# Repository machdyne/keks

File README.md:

# Keks Game Console

Keks is a 32-bit FPGA-based video game console and computer designed as a fun educational platform for teaching and learning about computers, electronics, FPGAs and programming.

This repo contains schematics, PCB layouts, pinouts, firmware, gateware, documentation and a 3D printable case.

Find more information on the [Keks product page](https://machdyne.com/product/keks-game-console/).

## Blinky 

Building the blinky example requires [Yosys](https://github.com/YosysHQ/yosys), [nextpnr-ice40](https://github.com/YosysHQ/nextpnr) and [IceStorm](https://github.com/YosysHQ/icestorm).

Assuming they are installed, you can simply type `make` to build the gateware, which will be written to output/blinky.bin. You can then connect the USB-C port to your computer and use the latest version of [ldprog](https://github.com/machdyne/ldprog) to write the gateware to the device.

## Programming

The RP2040 firmware and FPGA SRAM can be programmed over the USB-C port.

Configure the FPGA SRAM:

```
$ ldprog -k -s blinky.bin
```

It should also be possible to transfer gateware and games to the MicroSD card over the USB-C port but this is not yet implemented.

## Games

* [pong](games/pong)

## Firmware

Keks ships with RP2040 [firmware](firmware) based on the [Müsli](https://github.com/machdyne/musli) firmware which allows it to communicate with [ldprog](https://github.com/machdyne/ldprog).

The firmware is responsible for initializing the system, [configuring and outputting the RP clock](https://www.raspberrypi.com/documentation/pico-sdk/hardware.html#hardware_clocks), configuring the FPGA and detecting USB HID events.

The RP clock (CLK\_RP) is 48MHz by default. Keks also has a 100 MHz oscillator on board (CLK\_100).

*The following description is still under development and may change.*

*If an inserted FAT-formatted MicroSD card contains a bitstream file in the root directory named GATEWARE.BIN it will be used to configure the FPGA after power-on.*

*The RP2040 firmware also acts as an SPI master and sends updates to the FPGA when the status of the gamepads/joysticks change.*

In addition to the 4 CSPI signals and CLK\_RP there are 6 other signals connected to both the RP2040 and the FPGA: RP\_TX, RP\_RX, and RP\_INT, CDONE, CRESET and BTN.

### Updating the Firmware

To build the latest firmware you will need to install the [Raspberry Pi Pico SDK](https://github.com/raspberrypi/pico-sdk).

Set the `PICO_SDK_PATH` environment variable to your SDK path.

```
$ git clone https://github.com/machdyne/keks
$ cd keks/firmware/keks
$ mkdir build
$ cd build
$ cmake ..
$ make
```

The firmware can then be updated by holding down the (small) BOOTSEL button, connecting the USB-C port to your computer, and then dragging and dropping a new UF2 file to the device filesystem.

## DDMI

See this [my_hdmi_device fork](https://github.com/machdyne/my_hdmi_device) for an example of outputting video on the DDMI port.

See this [SmolDVI fork](https://github.com/machdyne/SmolDVI) for another example of outputting video on the DDMI port.

## Pinouts

 * [DDMI](https://github.com/machdyne/ddmi)

## License

The contents of this repo are released under the [Lone Dynamics Open License](LICENSE.md) with the following exceptions:

- The KiCad design files contain parts of the [kicad-pmod](https://github.com/mithro/kicad-pmod) library which is released under the [Apache License, Version 2.0](https://www.apache.org/licenses/LICENSE-2.0.html).

- The KiCad design files may contain symbols and footprints released under other licenses; please contact us if we've failed to give proper attribution.

Note: You can use these designs for commercial purposes but we ask that instead of producing exact clones, that you either replace our trademarks and logos with your own or add your own next to ours.

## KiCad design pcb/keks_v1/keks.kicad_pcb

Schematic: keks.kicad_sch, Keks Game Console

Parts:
C1, C2, C4, C5, C9, C10, C12, C14, C15, C19, C32, C39, C57, C58: 100nF; C_0603_1608Metric
C3, C6, C33, C35, C37, C41, C63, C64: 1uF; C_0603_1608Metric
C7, C34, C36: 100nF; C_0402_1005Metric
C8, C21, C25, C26, C27, C28, C29: 10nF; C_0603_1608Metric
C11, C16, C20, C22, C23: 220nF; C_0603_1608Metric
C13, C30, C31, C56: 4.7uF; R_0603_1608Metric
C17, C18, C60, C61: 10uF; C_0603_1608Metric
C24: 10nF; C_0402_1005Metric
C38, C40: 15pF; C_0603_1608Metric
C42, C49, C55: 1uF; R_0603_1608Metric
C43, C44, C45, C46, C47, C48, C50, C51, C52, C53, C54, C62: 100nF; R_0603_1608Metric
C59: 10uF; R_0603_1608Metric
C65, C66, C67, C68: 22uF; C_0603_1608Metric
D1: D_Schottky_Small; D_0603_1608Metric
D2: LED_RGB_ANODE; LED_RGB_0606_CHANZON
D3: LED; LED_0603_1608Metric
FB1, FB2, FB3: Ferrite_Bead; R_0603_1608Metric
H1, H2, H3, H4: MountingHole_Pad; MountingHole_3.2mm_M3_Pad
J1: TYPE-C-31-M-12-FIXED; USB_C_Receptacle_HRO_TYPE-C-31-M-12-BIG-PADS; PARTREV A
J2, J3: USB_A; USB_A_Stewart_SS-52100-001_Horizontal
J4: VIDEO; Generic_Chinese_RCA_Jack_FIXED
J5: AUDIO_LEFT; Generic_Chinese_RCA_Jack_FIXED
J6: AUDIO_RIGHT; Generic_Chinese_RCA_Jack_FIXED
J7: MICROSD; SDCARD
J8: Conn_01x02_Male; PinHeader_1x02_P2.54mm_Vertical
J9: HDMI_A; HDMI_TE_1827059-3-FIXED
L1, L2: 1uH; L_0603_1608Metric
PMOD1: PMOD-Device-x2-Type-1A-GPIO; PMOD_2x06_HOST_VERTICAL
PMOD2: PMOD-Device-x2-Type-1A-GPIO; PMOD_2x06_HOST
R1, R7: 5K1; R_0603_1608Metric
R2, R3: 27R; R_0603_1608Metric
R4, R5, R6, R8, R16: 10K; R_0603_1608Metric
R9, R10, R22, R23: 100R; R_0603_1608Metric
R11, R12, R13, R14: 22R; R_0603_1608Metric
R15: 1K; R_0402_1005Metric
R17, R20: 1K; R_0603_1608Metric
R18, R35, R36, R37, R38, R39, R40, R41, R42: 270R; R_0603_1608Metric
R19, R25, R27, R29, R33: 536R; R_0603_1608Metric
R21: 2K2; R_0603_1608Metric
R24: 33R; R_0603_1608Metric
R26, R28, R30, R31, R32, R34: 20K; R_0603_1608Metric
R43: 210K; R_0603_1608Metric
R44: 47K; R_0603_1608Metric
R45, R46: 200K; R_0603_1608Metric
SW1: SW_Push; Button_2P_3x4mm
SW2: SW_Push; SW_Cherry_MX_1.00u_PCB
TP1: TP_PWR5V0; TestPoint_THTPad_D1.0mm_Drill0.5mm
TP2, TP3, TP4, TP5, TP6, TP7, TP8, TP9: TestPoint; TestPoint_Pad_1.0x1.0mm
TP10: TP_PWR1V8; TestPoint_THTPad_D1.0mm_Drill0.5mm
TP11, TP12: TestPoint; TestPoint_THTPad_D1.0mm_Drill0.5mm
U1: ICE40HX8K-CT256; BGA256C80P16X16_1400X1400X170; PART_REV 3.4
U2, U3: IS61WV256; BGA48C75P8X6_800X600X120N
U4: RP2040; RP2040-QFN-56-OFFICIAL; PARTREV 1.6.1
U5: APS256; APS256_BGA_24
U6: AT25SF081-SSHD-X; SOIC-8_3.9x4.9mm_P1.27mm
U7: NCP164ASN180T1G; TSOP-5_1.65x3.05mm_P0.95mm
U8, U9: AP61300Z6-7; SOT-563
Y1: ECS-80-12-33-JGN-TR-12MHZ; XTAL_ECS-240-8-33-AGN-TR
Y2: KC2016Z100; OSC_KC2016Z13.5600C1KX00; PARTREV November 2020

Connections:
/BUTTON: SW2.1, U1.A6 (IOT_211), U4.40 (GPIO28/ADC2)
/CDONE: R6.1, U1.M10 (CDONE), U4.34 (GPIO22)
/CK_N: J9.12 (CK-), R42.2
/CK_P: J9.10 (CK+), R41.2
/CLK100: U1.F7 (IOT_198_GBIN0), Y2.3 (OUTPUT)
/COMP_D0: R18.1, U1.T1 (IOB_53)
/COMP_D1: R19.1, U1.R2 (IOB_55)
/COMP_D2: R20.1, U1.T2 (IOB_57)
/COMP_D3: R21.1, U1.R3 (IOB_59)
/COMP_OUT: J4.1 (In), R24.2
/CRESET: R8.1, U1.N11 (CRESET_B), U4.35 (GPIO23)
/CSPI_SCK: R5.1, U1.R11 (IOB_107_SCK), U4.38 (GPIO26/ADC0)
/CSPI_SI: U1.P11 (IOB_106_SDI), U4.39 (GPIO27/ADC1)
/CSPI_SO: U1.P12 (IOB_105_SDO), U4.36 (GPIO24)
/CSPI_SS: R4.1, U1.R12 (IOB_108_SS), U4.37 (GPIO25)
/D0_N: J9.9 (D0-), R40.2
/D0_P: J9.7 (D0+), R39.2
/D1_N: J9.6 (D1-), R38.2
/D1_P: J9.4 (D1+), R37.2
/D2_N: J9.3 (D2-), R36.2
/D2_P: J9.1 (D2+), R35.2
/DVI_CK_N: R42.1, U1.T5 (IOB_69)
/DVI_CK_P: R41.1, U1.T6 (IOB_73)
/DVI_D0_N: R40.1, U1.T7 (IOB_75)
/DVI_D0_P: R39.1, U1.T8 (IOB_76)
/DVI_D1_N: R38.1, U1.T9 (IOB_79)
/DVI_D1_P: R37.1, U1.T10 (IOB_88)
/DVI_D2_N: R36.1, U1.T13 (IOB_94)
/DVI_D2_P: R35.1, U1.T14 (IOB_92)
/HRAM_ADQ0: U1.L16 (IOR_127), U5.D3 (ADQ0)
/HRAM_ADQ1: U1.K16 (IOR_133), U5.D2 (ADQ1)
/HRAM_ADQ2: U1.K14 (IOR_129), U5.C4 (ADQ2)
/HRAM_ADQ3: U1.M15 (IOR_123), U5.D4 (ADQ3)
/HRAM_ADQ4: U1.P16 (IOR_113), U5.D5 (ADQ4)
/HRAM_ADQ5: U1.N16 (IOR_117), U5.E3 (ADQ5)
/HRAM_ADQ6: U1.M16 (IOR_121), U5.E2 (ADQ6)
/HRAM_ADQ7: U1.K15 (IOR_131), U5.E1 (ADQ7)
/HRAM_CE: U1.E16 (IOR_151), U5.A3 (CE#)
/HRAM_CK: U1.J15 (IOR_130), U5.B2 (CK)
/HRAM_DQ8: U1.J14 (IOR_134), U5.C2 (DQ8)
/HRAM_DQ9: U1.J16 (IOR_138), U5.B1 (DQ9)
/HRAM_DQ10: U1.E14 (IOR_160), U5.A2 (DQ10)
/HRAM_DQ11: U1.D16 (IOR_153), U5.A4 (DQ11)
/HRAM_DQ12: U1.D15 (IOR_157), U5.A5 (DQ12)
/HRAM_DQ13: U1.F14 (IOR_155), U5.B4 (DQ13)
/HRAM_DQ14: U1.F15 (IOR_149), U5.B5 (DQ14)
/HRAM_DQ15: U1.L14 (IOR_119), U5.C5 (DQ15)
/HRAM_DQS0: U1.K13 (IOR_128), U5.C3 (DQSDM0)
/HRAM_DQS1: U1.H14 (IOR_142), U5.B3 (DQSDM1)
/LED: R33.2, U1.A5 (IOT_213)
/LEDC_B: D2.2 (BK), R29.1
/LEDC_G: D2.4 (GK), R27.1
/LEDC_R: D2.3 (RK), R25.1
/LED_B: R29.2, U4.31 (GPIO20)
/LED_G: R27.2, U4.30 (GPIO19)
/LED_R: R25.2, U4.29 (GPIO18)
/PMOD_A1: PMOD1.1 (IOA0), U1.A11 (IOT_187)
/PMOD_A2: PMOD1.2 (IOA1), U1.B13 (IOT_178)
/PMOD_A3: PMOD1.3 (IOA2), U1.A15 (IOT_177)
/PMOD_A4: PMOD1.4 (IOA3), U1.A16 (IOT_176)
/PMOD_A7: PMOD1.7 (IOB0), U1.B12 (IOT_182)
/PMOD_A8: PMOD1.8 (IOB1), U1.B14 (IOT_171)
/PMOD_A9: PMOD1.9 (IOB2), U1.B15 (IOT_169)
/PMOD_A10: PMOD1.10 (IOB3), U1.C14 (IOT_168)
/PMOD_B1: PMOD2.1 (IOA0), U1.M12 (IOB_101)
/PMOD_B2: PMOD2.2 (IOA1), U1.T16 (IOB_100)
/PMOD_B3: PMOD2.3 (IOA2), U1.R10 (IOB_84)
/PMOD_B4: PMOD2.4 (IOA3), U1.P10 (IOB_86)
/PMOD_B7: PMOD2.7 (IOB0), U1.R16 (IOB_102)
/PMOD_B8: PMOD2.8 (IOB1), U1.T15 (IOB_91)
/PMOD_B9: PMOD2.9 (IOB2), U1.P13 (IOB_104_CBSEL1)
/PMOD_B10: PMOD2.10 (IOB3), U1.T11 (IOB_89)
/PWM_LEFT: R22.1, U1.T3 (IOB_61)
/PWM_LEFT_OUT: C60.1, J5.1 (In)
/PWM_RIGHT: R23.1, U1.R4 (IOB_63)
/PWM_RIGHT_OUT: C61.1, J6.1 (In)
/PWR1V1: C46.1, C48.1, C49.1, U4.23 (DVDD), U4.45 (VREG_VOUT), U4.50 (DVDD)
/PWR1V2: C3.1, C6.1, C11.1, C16.1, C20.1, C22.1, C23.1, C26.1, C28.1, C29.1, C68.1, L2.2, R9.1, R10.1, R45.1, TP12.1, U1.A14 (VCC), U1.F6 (VCC), U1.F10 (VCC), U1.K6 (VCC), U1.K10 (VCC), U1.L2 (VCC), U8.5 (EN), U9.6 (OUT)
/PWR1V8: C2.1, C5.1, C8.1, C52.2, C53.2, C56.2, C64.1, TP10.1, U1.C15 (VCCIO_1), U1.H10 (VCCIO_1), U1.H15 (VCCIO_1), U1.N15 (VCCIO_1), U5.D1 (VDD), U5.E4 (VDD1), U7.5 (OUT)
/PWR2V5: C10.1, D1.1 (K), U1.E12 (VPP_2V5)
/PWR3V3: C1.1, C4.1, C7.1, C9.1, C12.1, C19.1, C21.1, C24.1, C25.1, C27.1, C32.2, C33.2, C34.2, C35.2, C36.2, C37.2, C39.2, C41.2, C42.1, C43.1, C44.1, C45.1, C47.1, C50.1, C51.1, C54.1, C55.1, C59.1, C62.1, C63.1, C67.1, D1.2 (A), D2.1 (A), D3.2 (A), J7.4 (VDD), L1.2, PMOD1.6 (VCC), PMOD1.12 (VCC), PMOD2.6 (VCC), PMOD2.12 (VCC), R4.2, R5.2, R6.2, R8.2, R16.2, R26.1, R28.1, R30.1, R31.1, R32.1, R34.1, R43.1, TP11.1, U1.A3 (VCCIO_0), U1.A8 (VCCIO_0), U1.A13 (VCCIO_0), U1.E1 (VCCIO_3), U1.F8 (VCCIO_0), U1.G6 (VCCIO_3), U1.J6 (VCCIO_3), U1.K8 (VCCIO_2), U1.N1 (VCCIO_3), U1.N13 (VCC_SPI), U1.P3 (VCCIO_2), U1.R8 (VCCIO_2), U1.R13 (VCCIO_2), U2.D6 (VDD2), U2.E1 (VDD1), U3.D6 (VDD2), U3.E1 (VDD1), U4.1 (IOVDD), U4.10 (IOVDD), U4.22 (IOVDD), U4.26 (RUN), U4.33 (IOVDD), U4.42 (IOVDD), U4.43 (ADC_AVDD), U4.44 (VREG_VIN), U4.48 (USB_VDD), U4.49 (IOVDD), U6.8 (VCC), U7.1 (IN), U7.3 (EN), U8.6 (OUT), Y2.1 (INH), Y2.4 (VCC)
/PWR5V0: C13.1, C30.1, C31.1, C65.1, C66.1, FB1.1, FB2.1, FB3.1, J8.1, J9.18 (+5V), TP1.1, U8.3 (VIN), U9.3 (VIN), U9.5 (EN)
/RP_CLK: U1.K9 (IOB_82_GBIN4), U4.32 (GPIO21)
/RP_INT: U1.D9 (IOT_193), U4.41 (GPIO29/ADC3)
/RP_RX: U1.L7 (IOL_21A), U4.28 (GPIO17)
/RP_TX: U1.L6 (IOL_19A), U4.27 (GPIO16)
/RSPI_IO0: TP5.1, U4.53 (QSPI_SD0), U6.5 (SI/IO0)
/RSPI_IO1: TP6.1, U4.55 (QSPI_SD1), U6.2 (SO/IO1)
/RSPI_IO2: TP7.1, U4.54 (QSPI_SD2), U6.3 (~WP/IO2)
/RSPI_IO3: TP8.1, U4.51 (QSPI_SD3), U6.7 (~HOLD/IO3)
/RSPI_SCK: TP9.1, U4.52 (QSPI_SCLK), U6.6 (SCK)
/RSPI_SS: R16.1, R17.2, TP4.1, U4.56 (QSPI_CSN), U6.1 (~CS)
/SD_DAT1: J7.8 (DAT1), R34.2
/SD_DAT2: J7.1 (DAT2), R32.2
/SD_MISO: J7.7 (DAT0), R26.2, U4.6 (GPIO4)
/SD_MOSI: J7.3 (CMD), R30.2, U4.9 (GPIO7)
/SD_SCK: J7.5 (CLK), R28.2, U4.8 (GPIO6)
/SD_SS: J7.2 (DAT3/CD), R31.2, U4.7 (GPIO5)
/SRAM0_CS: U1.G3 (IOL_8A), U2.B5 (~CS)
/SRAM0_D0: U1.J5 (IOL_13A), U2.B6 (D0)
/SRAM0_D1: U1.H5 (IOL_7A), U2.C5 (D1)
/SRAM0_D2: U1.H6 (IOL_10A), U2.C6 (D2)
/SRAM0_D3: U1.G5 (IOL_5A), U2.D5 (D3)
/SRAM0_D4: U1.G4 (IOL_6A), U2.E5 (D4)
/SRAM0_D5: U1.F1 (IOL_10B), U2.F5 (D5)
/SRAM0_D6: U1.E2 (IOL_7B), U2.F6 (D6)
/SRAM0_D7: U1.F2 (IOL_9B), U2.G6 (D7)
/SRAM0_D8: U1.F5 (IOL_2A), U2.B1 (D8)
/SRAM0_D9: U1.D1 (IOL_5B), U2.C1 (D9)
/SRAM0_D10: U1.E3 (IOL_6B), U2.C2 (D10)
/SRAM0_D11: U1.D2 (IOL_4B), U2.D2 (D11)
/SRAM0_D12: U1.C1 (IOL_3A), U2.E2 (D12)
/SRAM0_D13: U1.B1 (IOL_2B), U2.F2 (D13)
/SRAM0_D14: U1.C2 (IOL_3B), U2.F1 (D14)
/SRAM0_D15: U1.B2 (IOL_1B), U2.G1 (D15)
/SRAM0_LB: U1.F4 (IOL_4A), U2.A1 (~LB)
/SRAM0_OE: U1.F3 (IOL_8B), U2.A2 (~OE)
/SRAM0_UB: U1.E4 (IOL_1A), U2.B2 (~UB)
/SRAM0_WE: U1.G2 (IOL_11B), U2.G5 (~WE)
/SRAM1_CS: U1.P2 (IOL_25A), U3.B5 (~CS)
/SRAM1_D0: U1.R1 (IOL_26A), U3.B6 (D0)
/SRAM1_D1: U1.M3 (IOL_22B), U3.C5 (D1)
/SRAM1_D2: U1.M4 (IOL_24B), U3.C6 (D2)
/SRAM1_D3: U1.N4 (IOL_26B), U3.D5 (D3)
/SRAM1_D4: U1.K4 (IOL_18A), U3.E5 (D4)
/SRAM1_D5: U1.K5 (IOL_20A), U3.F5 (D5)
/SRAM1_D6: U1.L5 (IOL_23A), U3.F6 (D6)
/SRAM1_D7: U1.M5 (IOL_25B), U3.G6 (D7)
/SRAM1_D8: U1.M1 (IOL_18B), U3.B1 (D8)
/SRAM1_D9: U1.L1 (IOL_17B), U3.C1 (D9)
/SRAM1_D10: U1.M2 (IOL_20B), U3.C2 (D10)
/SRAM1_D11: U1.K1 (IOL_16A), U3.D2 (D11)
/SRAM1_D12: U1.K3 (IOL_16B), U3.E2 (D12)
/SRAM1_D13: U1.J2 (IOL_15A), U3.F2 (D13)
/SRAM1_D14: U1.J1 (IOL_15B), U3.F1 (D14)
/SRAM1_D15: U1.H1 (IOL_14B), U3.G1 (D15)
/SRAM1_LB: U1.N2 (IOL_21B), U3.A1 (~LB)
/SRAM1_OE: U1.P1 (IOL_24A), U3.A2 (~OE)
/SRAM1_UB: U1.N3 (IOL_23B), U3.B2 (~UB)
/SRAM1_WE: U1.M6 (IOL_22A), U3.G5 (~WE)
/SRAM_A0: U1.C5 (IOT_221), U2.A3 (A0), U3.A3 (A0)
/SRAM_A1: U1.C6 (IOT_209), U2.A4 (A1), U3.A4 (A1)
/SRAM_A2: U1.C7 (IOT_206), U2.A5 (A2), U3.A5 (A2)
/SRAM_A3: U1.B6 (IOT_208), U2.B3 (A3), U3.B3 (A3)
/SRAM_A4: U1.B5 (IOT_214), U2.B4 (A4), U3.B4 (A4)
/SRAM_A5: U1.B4 (IOT_216), U2.C3 (A5), U3.C3 (A5)
/SRAM_A6: U1.B3 (IOT_223), U2.C4 (A6), U3.C4 (A6)
/SRAM_A7: U1.A1 (IOT_220), U2.D4 (A7), U3.D4 (A7)
/SRAM_A8: U1.C10 (IOT_185), U2.H2 (A8), U3.H2 (A8)
/SRAM_A9: U1.C11 (IOT_180), U2.H3 (A9), U3.H3 (A9)
/SRAM_A10: U1.A10 (IOT_186), U2.H4 (A10), U3.H4 (A10)
/SRAM_A11: U1.B11 (IOT_184), U2.H5 (A11), U3.H5 (A11)
/SRAM_A12: U1.B9 (IOT_199), U2.G3 (A12), U3.G3 (A12)
/SRAM_A13: U1.A9 (IOT_194), U2.G4 (A13), U3.G4 (A13)
/SRAM_A14: U1.B10 (IOT_183), U2.F3 (A14), U3.F3 (A14)
/SRAM_A15: U1.C9 (IOT_191), U2.F4 (A15), U3.F4 (A15)
/SRAM_A16: U1.A7 (IOT_205), U2.E4 (A16), U3.E4 (A16)
/SRAM_A17: U1.A2 (IOT_218), U2.D3 (A17), U3.D3 (A17)
/SWCLK: TP2.1, U4.24 (SWCLK)
/SWDIO: TP3.1, U4.25 (SWD)
/USB2_CONN_DN: J2.2 (D-), R12.2
/USB2_CONN_DP: J2.3 (D+), R11.2
/USB2_DN: R12.1, U4.17 (GPIO14)
/USB2_DP: R11.1, U4.16 (GPIO13)
/USB3_CONN_DN: J3.2 (D-), R14.1
/USB3_CONN_DP: J3.3 (D+), R13.1
/USB3_DN: R14.2, U4.3 (GPIO1)
/USB3_DP: R13.2, U4.2 (GPIO0)
/USB_CONN_DN: J1.A7 (DN1), J1.B7 (DN2), R2.1
/USB_CONN_DP: J1.A6 (DP1), J1.B6 (DP2), R3.1
/USB_DN: R2.2, U4.46 (USB_DM)
/USB_DP: R3.2, U4.47 (USB_DP)
/XIN: C38.2, U4.20 (XIN), Y1.1 (IN/OUT)
/XOUT: R15.1, U4.21 (XOUT)
GND: C1.2, C2.2, C3.2, C4.2, C5.2, C6.2, C7.2, C8.2, C9.2, C10.2, C11.2, C12.2, C13.2, C16.2, C19.2, C20.2, C21.2, C22.2, C23.2, C24.2, C25.2, C26.2, C27.2, C28.2, C29.2, C30.2, C31.2, C32.1, C33.1, C34.1, C35.1, C36.1, C37.1, C38.1, C39.1, C40.2, C41.1, C42.2, C43.2, C44.2, C45.2, C46.2, C47.2, C48.2, C49.2, C50.2, C51.2, C52.1, C53.1, C54.2, C55.2, C56.1, C57.1, C58.1, C59.2, C62.2, C63.2, C64.2, C65.2, C66.2, C67.2, C68.2, H1.1, H2.1, H3.1, H4.1, J1.A1 (GND), J1.A12 (GND), J1.B1 (GND), J1.B12 (GND), J1.S1 (SHIELD), J1.S2 (SHIELD), J1.S3 (SHIELD), J1.S4 (SHIELD), J2.4 (GND), J2.5 (Shield), J3.4 (GND), J3.5 (Shield), J4.2 (Ext), J5.2 (Ext), J6.2 (Ext), J7.6 (VSS), J8.2, J9.2 (D2S), J9.5 (D1S), J9.8 (D0S), J9.11 (CKS), J9.17 (GND), J9.S1 (SH), J9.S2 (SH), J9.S3 (SH), J9.S4 (SH), PMOD1.5 (GND), PMOD1.11 (GND), PMOD2.5 (GND), PMOD2.11 (GND), R1.2, R7.2, R44.2, R46.2, SW1.2, SW2.2, U1.A4 (GND), U1.A12 (GND), U1.E15 (GND), U1.G7 (GND), U1.G8 (GND), U1.G9 (GND), U1.H7 (GND), U1.H8 (GND), U1.H9 (GND), U1.J7 (GND), U1.J8 (GND), U1.J9 (GND), U1.K2 (GND), U1.K7 (GND), U1.L15 (GND), U1.R7 (GND), U1.T4 (GND), U1.T12 (GND), U2.D1 (VSS1), U2.E6 (VSS2), U3.D1 (VSS1), U3.E6 (VSS2), U4.19 (TESTEN), U4.57 (GND), U5.C1 (VSS), U5.E5 (VSS1), U6.4 (GND), U7.2 (GND), U8.2 (GND), U9.2 (GND), Y1.2 (GND), Y1.4 (GND), Y2.2 (CASE_GND)
unnamed: C14.1, C17.1, R9.2, U1.L8 (VCCPLL0)
unnamed: C14.2, C17.2, U1.N8 (GNDPLL0)
unnamed: C15.1, C18.1, R10.2, U1.E8 (VCCPLL1)
unnamed: C15.2, C18.2, U1.E7 (GNDPLL1)
unnamed: C40.1, R15.2, Y1.3 (OUT/IN)
unnamed: C57.2, C60.2, R22.2
unnamed: C58.2, C61.2, R23.2
unnamed: D3.1 (K), R33.1
unnamed: FB1.2, J1.A4 (VBUS), J1.A9 (VBUS), J1.B4 (VBUS), J1.B9 (VBUS)
unnamed: FB2.2, J2.1 (VBUS)
unnamed: FB3.2, J3.1 (VBUS)
unnamed: J1.A5 (CC1), R1.1
unnamed: J1.B5 (CC2), R7.1
unnamed: L1.1, U8.4 (SW)
unnamed: L2.1, U9.4 (SW)
unnamed: R17.1, SW1.1
unnamed: R18.2, R19.2, R20.2, R21.2, R24.1
unnamed: R43.2, R44.1, U8.1 (FB)
unnamed: R45.2, R46.1, U9.1 (FB)

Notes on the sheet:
3V3
USB3: RP2040 USB HOST (PIO)
0.6V * (1 + (210/47)) = 3.28V
C1=15pF, C2=15pF, CL=12pF, Cstray=5, (C1*C2)/(C1+C2)+Cstray == CL
0.6V * (1 + (200/200)) = 1.2V
K E K S
1V8
USB2: RP2040 USB HOST (PIO)
USB1: POWER & RP2040 USB DEVICE

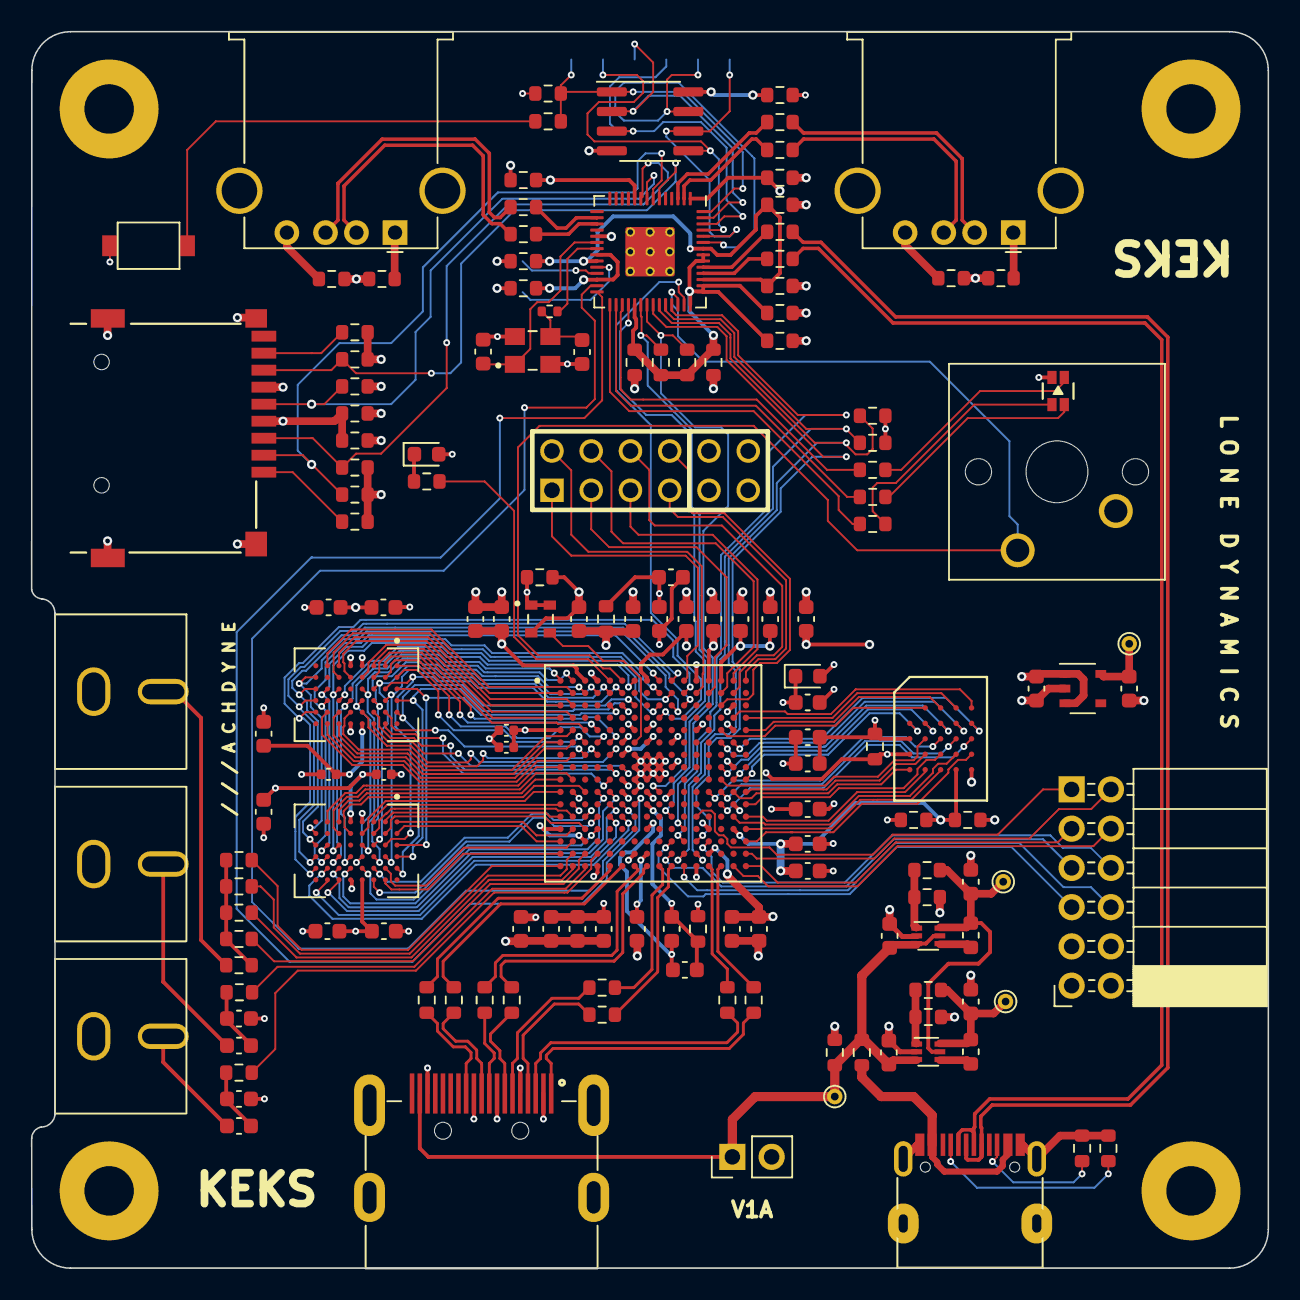
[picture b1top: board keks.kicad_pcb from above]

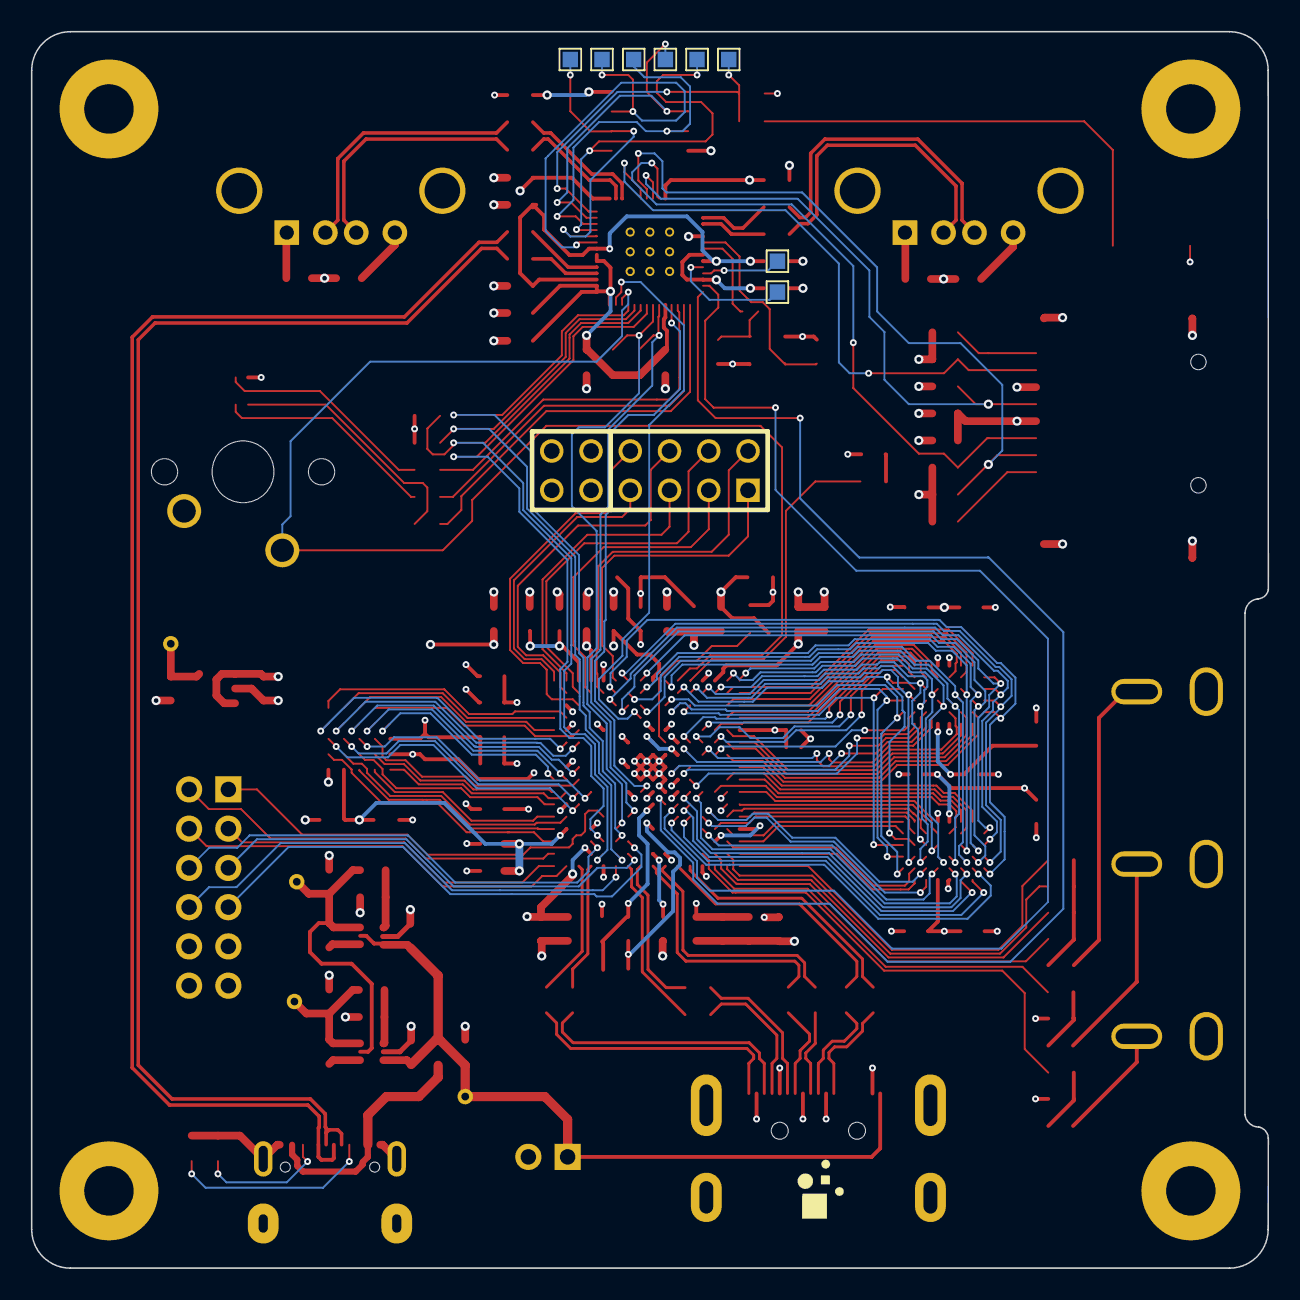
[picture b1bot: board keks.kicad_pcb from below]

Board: 4 copper layers, 80.0 x 80.0 mm, 162 parts (8 on the bottom side), 194 nets.

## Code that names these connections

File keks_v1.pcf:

# Keks V1
# -------

set_io CLK_100		F7
set_io CLK_RP		K9

set_io LED			A5
set_io BTN			A6

# PMOD A
set_io PMOD_A1		A11
set_io PMOD_A2		B13
set_io PMOD_A3		A15
set_io PMOD_A4		A16
set_io PMOD_A7		B12
set_io PMOD_A8		B14
set_io PMOD_A9		B15
set_io PMOD_A10	C14

# PMODB
set_io PMOD_B1		M12
set_io PMOD_B2		T16
set_io PMOD_B3		R10
set_io PMOD_B4		P10
set_io PMOD_B7		R16
set_io PMOD_B8		T15
set_io PMOD_B9		P13
set_io PMOD_B10	T11

# USB-UART on PMODB
set_io UART0_RTS  M12
set_io UART0_RX   T16
set_io UART0_TX   R10
set_io UART0_CTS  P10

# RP2040
set_io RP_TX		L6
set_io RP_RX		L7
set_io RP_INT		D9

# SRAM
set_io SRAM_A0		C5
set_io SRAM_A1		C6
set_io SRAM_A2		C7
set_io SRAM_A3		B6
set_io SRAM_A4		B5
set_io SRAM_A5		B4
set_io SRAM_A6		B3
set_io SRAM_A7		A1
set_io SRAM_A8		C10
set_io SRAM_A9		C11
set_io SRAM_A10	A10
set_io SRAM_A11	B11
set_io SRAM_A12	B9
set_io SRAM_A13	A9
set_io SRAM_A14	B10
set_io SRAM_A15	C9
set_io SRAM_A16	A7
set_io SRAM_A17	A2

set_io SRAM0_D0	J5
set_io SRAM0_D1	H5
set_io SRAM0_D2	H6
set_io SRAM0_D3	G5
set_io SRAM0_D4	G4
set_io SRAM0_D5	F1
set_io SRAM0_D6	E2
set_io SRAM0_D7	F2
set_io SRAM0_D8	F5
set_io SRAM0_D9	D1
set_io SRAM0_D10	E3
set_io SRAM0_D11	D2
set_io SRAM0_D12	C1
set_io SRAM0_D13	B1
set_io SRAM0_D14	C2
set_io SRAM0_D15	B2

set_io SRAM0_CE	G3
set_io SRAM0_OE	F3
set_io SRAM0_WE	G2
set_io SRAM0_UB	E4
set_io SRAM0_LB	F4

set_io SRAM1_D0	R1
set_io SRAM1_D1	M3
set_io SRAM1_D2	M4
set_io SRAM1_D3	N4
set_io SRAM1_D4	K4
set_io SRAM1_D5	K5
set_io SRAM1_D6	L5
set_io SRAM1_D7	M5
set_io SRAM1_D8	M1
set_io SRAM1_D9	L1
set_io SRAM1_D10	M2
set_io SRAM1_D11	K1
set_io SRAM1_D12	K3
set_io SRAM1_D13	J2
set_io SRAM1_D14	J1
set_io SRAM1_D15	H1

set_io SRAM1_CE	P2
set_io SRAM1_OE	P1
set_io SRAM1_WE	M6
set_io SRAM1_UB	N3
set_io SRAM1_LB	N2

# OPI PSRAM
set_io HRAM_ADQ0	L16
set_io HRAM_ADQ1	K16
set_io HRAM_ADQ2	K14
set_io HRAM_ADQ3	M15
set_io HRAM_ADQ4	P16
set_io HRAM_ADQ5	N16
set_io HRAM_ADQ6	M16
set_io HRAM_ADQ7	K15
set_io HRAM_DQ8	J14
set_io HRAM_DQ9	J16
set_io HRAM_DQ10	E14
set_io HRAM_DQ11	D16
set_io HRAM_DQ12	D15
set_io HRAM_DQ13	F14
set_io HRAM_DQ14	F15
set_io HRAM_DQ15	L14
set_io HRAM_CE		E16
set_io HRAM_CK		J15
set_io HRAM_DQS0	K13
set_io HRAM_DQS1	H14

# DDMI
set_io DDMI_D0_N	T7
set_io DDMI_D1_N	T9
set_io DDMI_D2_N	T13
set_io DDMI_CK_N	T5
set_io DDMI_D0_P	T8
set_io DDMI_D1_P	T10
set_io DDMI_D2_P	T14
set_io DDMI_CK_P	T6

# COMPOSITE VIDEO
set_io COMP_D0		T1
set_io COMP_D1		R2
set_io COMP_D2		T2
set_io COMP_D3		R3

# AUDIO
set_io AUDIO_L		T3
set_io AUDIO_R		R4

# CONFIG SPI
set_io CSPI_SS		R12
set_io CSPI_SCK	R11
set_io CSPI_SI		P11	# MISO
set_io CSPI_SO		P12	# MOSI
set_io CDONE		M10

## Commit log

2022-09-28 update firmware
2022-10-04 support fpga configuration from microsd card
2023-04-08 add pong
2023-04-08 add case
2023-05-10 add pcb

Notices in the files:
pcb/keks_v1/keks.kicad_sch:
Copyright © 2022 Lone Dynamics Corporation
